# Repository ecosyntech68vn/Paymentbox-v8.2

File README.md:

# EcoSynTech PaymentBox V8.2 — Complete Package

**Production-ready hardware + firmware** cho hệ thống tự động hóa thu tiền VietQR
qua phone Android + ESP32 watchdog.

Tác giả: TA QUANG THUAN — CEO/CTO EcoSynTech Global
Ngày: 20/05/2026

---

## Cấu trúc package

```
EcoSynTech_PaymentBox_V8.2_complete/
├── README.md                          ← Bạn đang đọc
├── docs/                              ← Documentation
│   ├── FEASIBILITY.md                  Đánh giá khả thi E và F
│   ├── AUDIT_V8_1.md                   11 lỗi tìm thấy trong V8.1
│   ├── 01_SCHEMATIC_V8_1.md            Schematic V8.1 (deprecated)
│   ├── 01_LAYOUT_V8_1.md               Layout V8.1 (deprecated)
│   ├── SCHEMATIC_V8_2.md               ★ Schematic V8.2 production
│   └── GAS_ENDPOINTS_V8_2.md           ★ Spec backend GAS hỗ trợ firmware
│
├── hardware/                          ← PCB V8.2 fab-ready
│   ├── paymentbox_v8_2_jlcpcb.zip      ★ Upload thẳng JLCPCB
│   ├── pcb_layout_v8_2.png             Layout visual (6 zones)
│   ├── board.step                      3D model cho case design
│   ├── board_top.pdf                   Top view PDF
│   ├── BOM_E_watchdog.csv              BOM phương án E
│   ├── BOM_F_full.csv                  BOM phương án F
│   ├── Pick_Place_F.csv                CPL cho SMT
│   ├── gerber/                         Gerber files
│   ├── drill/                          Drill files
│   ├── components_v8_2.py              Component placement source
│   └── nets_v8_2.py                    Netlist source
│
└── firmware/                          ← ESP-IDF V5.x firmware
    ├── README.md                       Build instructions
    ├── TEST_REPORT.md                  ★ 68/68 tests pass, 0 cppcheck warnings
    ├── CMakeLists.txt
    ├── sdkconfig.defaults
    ├── partitions.csv
    ├── main/
    │   ├── main.c                      Entry point
    │   └── include/paymentbox_config.h  Centralized config
    ├── tests/                          ★ Host-side unit tests
    │   ├── test_config_server.c        33 tests pass
    │   └── test_ota_updater.c          35 tests pass
    └── components/
        ├── event_bus/                  Pub/sub FreeRTOS queue
        ├── wifi_manager/               STA + AP fallback
        ├── config_server/              ★ HTTP form 192.168.4.1
        ├── ota_updater/                ★ esp_https_ota từ GAS
        ├── phone_poller/               Poll phone /health 30s
        ├── gas_poller/                 Poll GAS heartbeat 60s
        ├── led_status/                 5-state machine 3-LED PWM
        ├── buzzer/                     Beep patterns
        ├── lcd_ui/                     I2C LCD 16x2
        ├── battery_monitor/            ADC + USB-lost detection
        └── sd_logger/                  NDJSON log + rotation
```

│
└── backend/                          ← GAS V9.5 backend endpoints (mới 5/2026)
    └── gas_v9_5/
        ├── README.md                  Hướng dẫn deploy vào GAS Editor
        ├── TEST_REPORT.md             ★ 42/42 unit tests pass
        ├── gas_v9_5_paymentbox_endpoints.js  ★ Code copy vào GAS
        └── test_gas_endpoints.js      Node.js local tests

★ = milestone V8.2 production-ready

---

## Quick start — 4 bước

### 1. Order PCB (1 ngày)
Upload `hardware/paymentbox_v8_2_jlcpcb.zip` lên JLCPCB:
- 5 boards, 2-layer, ENIG, HASL, 1.6mm
- Cost: ~$8 + ship $10 = **~450k VND total**

### 2. Order components (1 ngày, song song)
Dùng `hardware/BOM_E_watchdog.csv` đặt LCSC hoặc Shopee VN:
- Tổng linh kiện E: **~193k VND** mỗi board
- Plus pin 18650 protected 2500mAh: +50k VND
- Plus phone Android cũ: +400k VND
→ **Tổng ~700k VND/unit**

### 3. Lắp ráp + test hardware (1 buổi)
Theo `docs/SCHEMATIC_V8_2.md` section 7 (Safety checklist 10 điểm).
- Cấp USB-C → đo +5V_SAFE = 4.8-4.9V
- Cắm pin đúng → BAT+ = 3-4.2V
- **Cắm pin ngược → +5V_SAFE = 0V** (verify chống ngược cực)

### 4. Build + flash firmware (30 phút)
```bash
cd firmware
. $IDF_PATH/export.sh
idf.py set-target esp32
idf.py build
idf.py -p /dev/ttyUSB0 flash monitor
```

Reboot lần đầu → AP "PaymentBox-Setup" → mở `http://192.168.4.1` → nhập WiFi + phone IP → reboot vào STA mode → vận hành.

---

## Tính năng đã có

✅ **Hardware**:
- ESP32-WROOM-32 + đầy đủ peripheral
- USB-C input + PPTC fuse + SMBJ5.0CA TVS (chống sét)
- AO3401 P-FET (chống ngược cực pin)
- TP4056 sạc Li-ion + MT3608 boost 3.7→5V
- Pin 18650 external qua JST connector
- ADC battery monitor + USB-lost detection
- 3 LED indicator + buzzer + LCD 16x2
- I2C bus mở rộng, SPI cho SD card
- (Optional F) ATECC608B HMAC + microSD + relay reset phone

✅ **Firmware** (2654 LOC C):
- Event bus FreeRTOS pub/sub 8 subscribers
- WiFi STA + AP fallback config
- **HTTP config server** captive portal (Vietnamese UTF-8 form)
- **OTA update từ GAS** với anti-downgrade + boot sanity 60s + rollback
- Phone health poller 30s
- GAS heartbeat poller 60s
- 5-state LED state machine (IDLE/OK/WARN/ALERT/CRITICAL)
- Buzzer alert patterns
- LCD UI 2Hz refresh
- Battery monitor ADC + USB-lost dV/dt detection
- SD logger NDJSON với rotation

✅ **Testing**:
- 68/68 host-side unit tests pass
- 0 cppcheck warnings (warning, style, performance, portability)
- Hardware test plan trong `firmware/TEST_REPORT.md`

---

## Chưa làm (TODO)

| Feature | Mức | Khi nào cần |
|---|---|---|
| ATECC608B driver firmware | High | Phương án F production |
| HMAC sign transaction trước khi push GAS | High | Phương án F |
| Battery check trước OTA (skip nếu < 3.5V) | Med | Sau khi field test 1 tháng |
| SHA256 verify firmware từ GAS | Med | Bảo mật cao hơn |
| Mobile app config qua BLE | Low | Phương án F UX nâng cao |
| 2.4" TFT thay LCD 16x2 | Low | Phương án F UX nâng cao |
| SOP conformal coating spray | High (production) | Trước khi giao khách F |
| Hộp ABS IP65 + EPDM gasket | High (production) | Trước khi giao khách F |

---

## Liên hệ

Mọi câu hỏi / báo lỗi → TA QUANG THUAN
- Telegram: @AIThucChien_bot (cho hỗ trợ)
- Email/SĐT: liên hệ EcoSynTech Global

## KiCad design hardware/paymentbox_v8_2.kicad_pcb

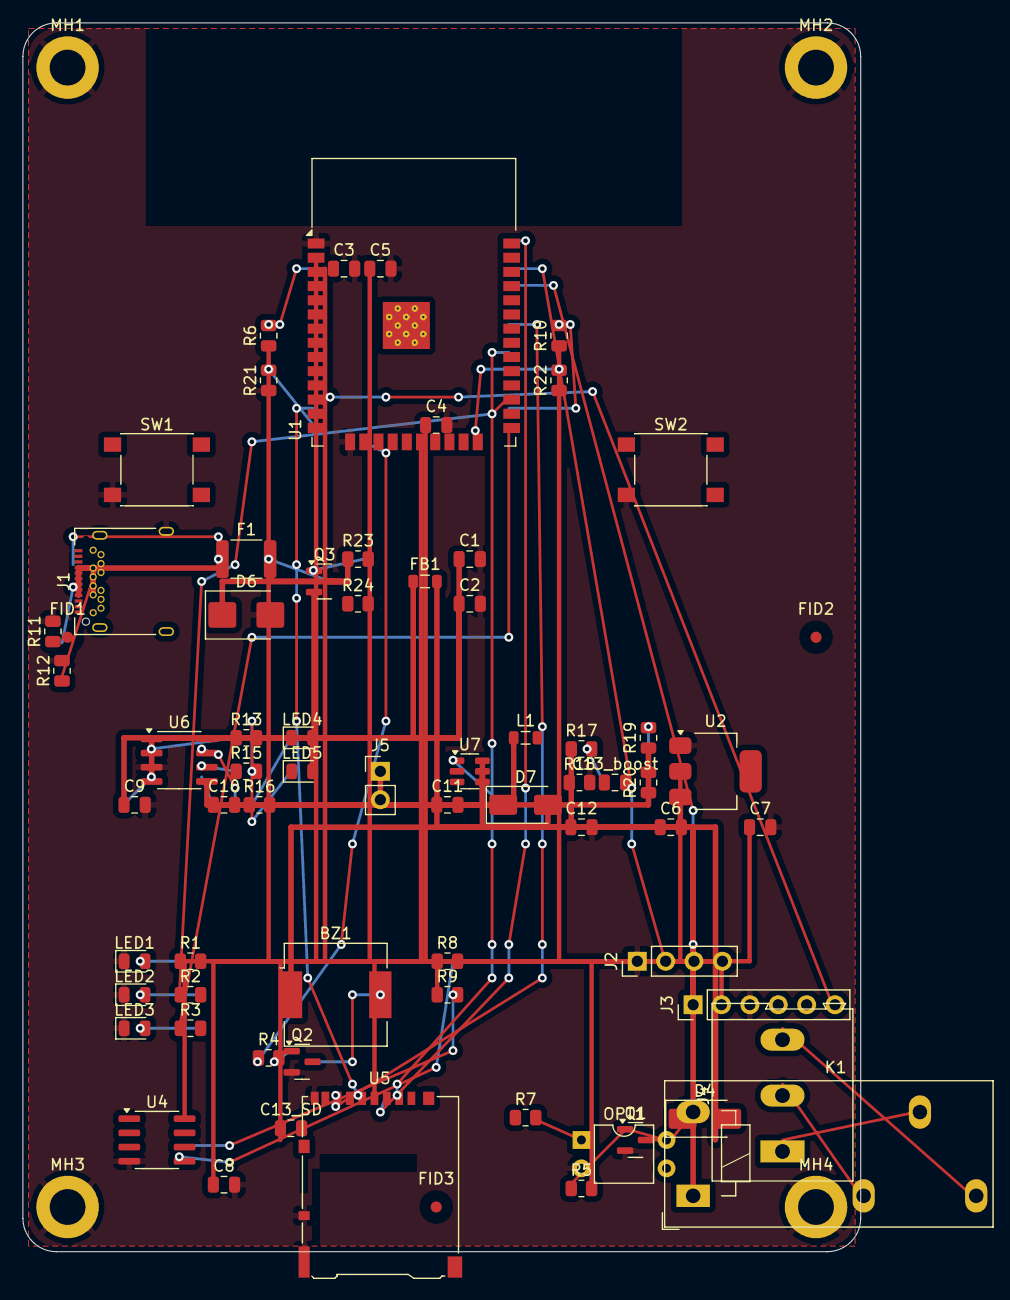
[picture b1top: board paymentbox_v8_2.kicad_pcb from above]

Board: 2 copper layers, 75.0 x 110.0 mm, 74 parts (0 on the bottom side), 45 nets.

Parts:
BZ1: BUZZER_5V; Buzzer_CUI_CPT-9019S-SMT
C1, C5, C9, C10, C13_SD: 10uF; C_0805_2012Metric
C2, C3, C4, C7, C8, C13_boost: 100nF; C_0805_2012Metric
C6, C11, C12: 22uF; C_0805_2012Metric
D4, D7: SS14; D_SMA
D6: SMBJ5.0CA; D_SMB
F1: PPTC_500mA; Fuse_1812_4532Metric
FB1: FB_1k; L_0805_2012Metric
FID1, FID2, FID3: FID; Fiducial_1mm_Mask3mm
J1: USB-C; USB_C_Receptacle_Amphenol_12401548E4-2A
J2: UART; PinHeader_1x04_P2.54mm_Vertical
J3: EXP; PinHeader_1x06_P2.54mm_Vertical
J4: RELAY_OUT; TerminalBlock_Altech_AK300-3_P5.00mm
J5: BAT; PinHeader_1x02_P2.54mm_Vertical
K1: SRD-05VDC; Relay_SPDT_Schrack-RT1-FormC_RM5mm
L1: 4.7uH; L_0805_2012Metric
LED1: RED; LED_0805_2012Metric
LED2: GREEN; LED_0805_2012Metric
LED3: BLUE; LED_0805_2012Metric
LED4: CHRG_RED; LED_0805_2012Metric
LED5: DONE_GRN; LED_0805_2012Metric
MH1, MH2, MH3, MH4: M3; MountingHole_3.2mm_M3_DIN965_Pad
OPT1: PC817; DIP-4_W7.62mm
Q1, Q2: MMBT3904; SOT-23
Q3: AO3401; SOT-23
R1, R2, R3: 220R; R_0805_2012Metric
R4, R5, R7, R15, R16: 1k; R_0805_2012Metric
R6, R10, R21, R22, R24: 10k; R_0805_2012Metric
R8, R9: 4.7k; R_0805_2012Metric
R11, R12: 5.1k; R_0805_2012Metric
R13: 1.2k; R_0805_2012Metric
R17: 22k; R_0805_2012Metric
R18: 3k; R_0805_2012Metric
R19, R23: 100k; R_0805_2012Metric
R20: 47k; R_0805_2012Metric
SW1: RESET; SW_Push_1P1T_NO_6x6mm_H9.5mm
SW2: BOOT; SW_Push_1P1T_NO_6x6mm_H9.5mm
U1: ESP32-WROOM-32
U2: AMS1117-3.3; SOT-223-3_TabPin2
U4: ATECC608B; SOIC-8_3.9x4.9mm_P1.27mm
U5: microSD; microSD_HC_Hirose_DM3AT-SF-PEJM5
U6: TP4056; SOIC-8_3.9x4.9mm_P1.27mm
U7: MT3608; SOT-23-6

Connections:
+3V3: C3.1, C4.1, C5.1, C7.1, C8.1, C13_SD.1, J2.4, J3.2, R5.2, R6.1, R8.1, R9.1, R10.1, U1.2, U1.20, U2.2, U4.8, U5.4
+5V_PROT_RAW: D6.1, F1.2, Q3.3, R23.1
+5V_SAFE: C1.1, C2.1, C9.1, FB1.1, LED4.2, LED5.2, Q3.2, U6.4
+5V_SYS: BZ1.1, C6.1, C12.1, D4.2, D7.2, FB1.2, J3.1, K1.A1, R17.1, U2.3, U7.5
+5V_USB_RAW: F1.1, J1.A4, J1.A9, J1.B4, J1.B9
ADC_BAT: R19.2, R20.1, U1.4
BAT+: C10.1, C11.1, J5.1, L1.1, R19.1, U6.5, U7.6
BOOST_FB: C13_boost.1, R17.2, R18.1, U7.3
BOOST_SW: D7.1, L1.2, U7.1
BUZZ_BASE: Q2.1, R4.2
BUZZ_COLLECTOR: BZ1.2, Q2.3
BUZZ_DRV: R4.1, U1.16
CHRG_LED: LED4.1, R16.2
CHRG_N: R16.1, U6.7
DONE_LED: LED5.1, R15.2
DONE_N: R15.1, U6.6
EN_RST: R6.2, SW1.1, U1.3
EXP_GPIO: J3.6, U1.12
GND: C1.2, C2.2, C3.2, C4.2, C5.2, C6.2, C7.2, C8.2, C9.2, C10.2, C11.2, C12.2, C13_SD.2, C13_boost.2, D6.2, J1.A1, J1.A12, J1.B1, J1.B12, J1.S1, J2.1, J3.3, J5.2, LED1.1, LED2.1, LED3.1, MH1.1, MH2.1, MH3.1, MH4.1, OPT1.2, Q1.2, Q2.2, R11.2, R12.2, R13.2, R18.2, R20.2, R21.1, R22.1, R24.2, SW1.2, SW2.2, U1.1, U1.15, U1.39, U2.1, U4.4, U5.6, U5.9, U5.10, U5.11, U6.3, U7.2
GPIO0_BOOT: R10.2, SW2.1, U1.26
I2C_SCL: J3.5, R9.2, U1.37, U4.6
I2C_SDA: J3.4, R8.2, U1.34, U4.5
LED_B_ANODE: LED3.2, R3.2
LED_B_DRV: R3.1, U1.25
LED_G_ANODE: LED2.2, R2.2
LED_G_DRV: R2.1, U1.27
LED_R_ANODE: LED1.2, R1.2
LED_R_DRV: R1.1, R21.2, U1.14
PROG: R13.1, U6.2
Q3_GATE: Q3.1, R23.2, R24.1
RELAY_COIL_LOW: D4.1, K1.A2, Q1.3
RELAY_COM: J4.1, K1.11
RELAY_DRV: R7.1, R22.2, U1.24
RELAY_NC: J4.2, K1.12
RELAY_NO: J4.3, K1.14
RELAY_OPTO_LED: OPT1.1, R7.2
RELAY_OPTO_OUT: OPT1.4, Q1.1, R5.1
SPI_CS_SD: U1.30, U5.2
SPI_MISO: U1.32, U5.7
SPI_MOSI: U1.38, U5.3
SPI_SCK: U1.13, U5.5
UART_RX: J2.3, U1.35
UART_TX: J2.2, U1.36
USB_CC1: J1.A5, R11.1
USB_CC2: J1.B5, R12.1

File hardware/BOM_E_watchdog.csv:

Comment,Designator,Footprint,LCSC Part #,Quantity
1.2k,R13,R_0805_2012Metric,C17520,1
100k,"R19,R23",R_0805_2012Metric,C17407,2
100nF,"C13_boost,C2,C3,C4,C7",C_0805_2012Metric,C49678,5
10k,"R10,R21,R22,R24,R6",R_0805_2012Metric,C17414,5
10uF,"C1,C10,C5,C9",C_0805_2012Metric,C15850,4
1k,"R15,R16,R4",R_0805_2012Metric,C17513,3
220R,"R1,R2,R3",R_0805_2012Metric,C17557,3
22k,R17,R_0805_2012Metric,C17557,1
22uF,"C11,C12,C6",C_0805_2012Metric,C45783,3
3k,R18,R_0805_2012Metric,C17561,1
4.7k,"R8,R9",R_0805_2012Metric,C17475,2
4.7uH,L1,L_0805_2012Metric,C407457,1
47k,R20,R_0805_2012Metric,C17475,1
5.1k,"R11,R12",R_0805_2012Metric,C23186,2
AMS1117-3.3,U2,SOT-223-3_TabPin2,C6186,1
AO3401,Q3,SOT-23,C15127,1
BAT,J5,PinHeader_1x02_P2.54mm_Vertical,C124375,1
BLUE,LED3,LED_0805_2012Metric,C72041,1
BOOT,SW2,SW_Push_1P1T_NO_6x6mm_H9.5mm,C318884,1
BUZZER_5V,BZ1,Buzzer_CUI_CPT-9019S-SMT,C95298,1
CHRG_RED,LED4,LED_0805_2012Metric,C84256,1
DONE_GRN,LED5,LED_0805_2012Metric,C72043,1
ESP32-WROOM-32,U1,ESP32-WROOM-32,C701343,1
EXP,J3,PinHeader_1x06_P2.54mm_Vertical,C124380,1
FB_1k,FB1,L_0805_2012Metric,C1017,1
GREEN,LED2,LED_0805_2012Metric,C72043,1
MMBT3904,Q2,SOT-23,C20526,1
MT3608,U7,SOT-23-6,C47773,1
PPTC_500mA,F1,Fuse_1812_4532Metric,C369317,1
RED,LED1,LED_0805_2012Metric,C84256,1
RESET,SW1,SW_Push_1P1T_NO_6x6mm_H9.5mm,C318884,1
SMBJ5.0CA,D6,D_SMB,C8975,1
SS14,D7,D_SMA,C2480,1
TP4056,U6,SOIC-8_3.9x4.9mm_P1.27mm,C16581,1
UART,J2,PinHeader_1x04_P2.54mm_Vertical,C124378,1
USB-C,J1,USB_C_Receptacle_Amphenol_12401548E4-2A,C168688,1

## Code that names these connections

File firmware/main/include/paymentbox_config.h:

/**
 * paymentbox_config.h — EcoSynTech PaymentBox V8.2 firmware config
 *
 * Tập trung MỌI hằng số tại đây. Không hardcode trong source.
 */
#pragma once

#include "driver/gpio.h"
#include "hal/adc_types.h"

// ============================================================
// VERSION
// ============================================================
#define FW_VERSION             "1.0.0"
#define FW_BUILD_DATE          __DATE__ " " __TIME__
#define HW_VERSION             "V8.2"

// ============================================================
// GPIO MAPPING — KHÔNG TỰ ĐỔI (phải đồng bộ với SCHEMATIC_V8_2.md)
// ============================================================

// LED status
#define PIN_LED_R              GPIO_NUM_12  // Đỏ — Sự cố
#define PIN_LED_G              GPIO_NUM_4   // Xanh lá — OK
#define PIN_LED_B              GPIO_NUM_2   // Xanh dương — Hoạt động

// Buzzer
#define PIN_BUZZER             GPIO_NUM_13

// Relay (phương án F only)
#define PIN_RELAY              GPIO_NUM_15

// I2C bus (LCD + ATECC608B)
#define PIN_I2C_SDA            GPIO_NUM_21
#define PIN_I2C_SCL            GPIO_NUM_22
#define I2C_PORT_NUM           I2C_NUM_0
#define I2C_FREQ_HZ            100000   // 100kHz
#define I2C_ADDR_LCD           0x27     // PCF8574 LCD backpack
#define I2C_ADDR_ATECC         0x60     // ATECC608B (F only)

// SPI bus (microSD)
#define PIN_SPI_SCK            GPIO_NUM_14
#define PIN_SPI_MOSI           GPIO_NUM_23
#define PIN_SPI_MISO           GPIO_NUM_19
#define PIN_SPI_CS_SD          GPIO_NUM_5

// ADC battery sense
#define PIN_ADC_BAT            ADC_CHANNEL_0   // GPIO36 / SENSOR_VP
#define BAT_DIVIDER_RATIO      3.13f           // V_BAT = ADC * 3.13

// UART debug
#define UART_NUM               UART_NUM_0
#define UART_BAUDRATE          115200

// ============================================================
// NETWORK
// ============================================================

// WiFi (qua wifi_manager — đọc từ NVS khi flash, hoặc qua AP config)
#define WIFI_DEFAULT_SSID      "EcoSynTech-Setup"
#define WIFI_DEFAULT_PSK       ""              // empty = open AP
#define WIFI_AP_FALLBACK_NAME  "PaymentBox-Setup"
#define WIFI_AP_PASSWORD       "ecosyntech"    // WPA2 PSK cho AP mode; đọc từ NVS key "wifi.ap_psk" nếu có
#define WIFI_CONNECT_TIMEOUT_MS 30000
#define WIFI_RECONNECT_DELAY_MS 5000

// Phone (BankNotify-App on Android)
// Tự discover qua mDNS hoặc set qua AP config UI
#define PHONE_DEFAULT_IP       "192.168.1.50"  // override via NVS
#define PHONE_HEALTH_URL       "http://%s:8765/api/v1/health"
#define PHONE_RECENT_URL       "http://%s:8765/api/v1/transactions/recent"
#define PHONE_POLL_INTERVAL_MS 60000           // 60s (1 phút quét 1 lần)
#define PHONE_TIMEOUT_MS       5000

// GAS backend (V9.5)
// Cần config khi flash production
#define GAS_BASE_URL           "https://script.google.com/macros/s/SHEET_ID/exec"
#define GAS_HEARTBEAT_PATH     "?action=getHeartbeat&device_id=%s"
#define GAS_POLL_INTERVAL_MS   60000           // 60s
#define GAS_TIMEOUT_MS         10000

// Telegram alert (optional — cần set token + chat_id trước khi dùng)
#define TELEGRAM_BOT_TOKEN      ""                // Bot token từ @BotFather — set trong NVS key "tg.token" nếu có
#define TELEGRAM_CHAT_ID        ""                // Chat ID để nhận alert — set trong NVS key "tg.chat_id"

// OTA update
#define OTA_CHECK_INTERVAL_MS  (24 * 3600 * 1000)   // 24h
#define OTA_CHECK_TIMEOUT_MS   15000
#define OTA_DOWNLOAD_TIMEOUT_MS 120000              // 2 phút
#define OTA_BOOT_SANITY_MS     60000                // Đợi 60s sau boot → mark valid

// Device identification
#define DEVICE_ID_PREFIX       "ESG-PB-"
#define DEVICE_ID_LEN          16              // ESG-PB-XXXXXXXX (8 hex từ MAC)

// ============================================================
// STATE MACHINE THRESHOLDS
// ============================================================

// Tính từ lần phone respond cuối:
#define HEALTH_OK_WINDOW_MS    60000           // <60s từ lần ping cuối = OK
#define HEALTH_WARN_WINDOW_MS  180000          // 1-3 phút = WARN (vàng)
#define HEALTH_ALERT_WINDOW_MS 300000          // 3-5 phút = ALERT (đỏ)
// > 5 phút = CRITICAL

// Battery thresholds
#define BAT_FULL_V             4.10f
#define BAT_LOW_V              3.40f
#define BAT_CRITICAL_V         3.00f

// ============================================================
// FREERTOS TASK CONFIG
// ============================================================
#define TASK_STACK_SMALL       2048
#define TASK_STACK_MEDIUM      4096
#define TASK_STACK_LARGE       8192

#define PRIO_LOW               2
#define PRIO_MED               5
#define PRIO_HIGH              10
#define PRIO_CRITICAL          15

// ============================================================
// SD CARD LOGGING
// ============================================================
#define SD_LOG_PATH            "/sdcard/paymentbox.log"
#define SD_LOG_MAX_BYTES       1048576         // 1MB → rotate
#define SD_LOG_ROTATE_KEEP     5               // keep 5 old logs

// ============================================================
// PROTOTYPING TOGGLES
// ============================================================
#define ENABLE_PHONE_POLLER    1
#define ENABLE_GAS_POLLER      1
#define ENABLE_LCD_UI          1
#define ENABLE_SD_LOG          0   // disable nếu phương án E không lắp SD
#define ENABLE_RELAY_CTRL      0   // F only — luôn 0 cho phương án E
#define ENABLE_BATTERY_MONITOR 1
#define ENABLE_CONFIG_SERVER   1   // HTTP server cho AP mode setup
#define ENABLE_OTA             1   // OTA firmware update qua GAS
#define ENABLE_TELEGRAM_ALERT  0   // Bật Telegram alert khi GAS down / bat critical

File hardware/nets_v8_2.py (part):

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        # Let me make it: +5V_SAFE in net carries LED5.2, then LED5.1 connects via R15 to TP4056 STDBY pin
    ],

    # TP4056 PROG (charge current set) — pin 2 to GND via R13
    "PROG_R": [
        ("U6", "2"),    # TP4056 PROG (pin 2)
        ("R13", "1"),
    ],
    # R13 high side wired in this net, low side to GND. Wait need separate:
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        ("SW1", "1"),   # Reset button
    ],

    "GPIO0_BOOT": [
        ("U1", "26"),
        ("R10", "2"),
        ("SW2", "1"),
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    # ============================================================
    # Expansion
    # ============================================================
    "EXP_GPIO": [("U1", "12"), ("J3", "6")],

    # ============================================================
    # +5V_SAFE special: PC817 emitter + R5 high side
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
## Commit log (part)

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2026-05-20 Audit V8.2: fix 24 bugs, add Quick Wins, Medium optimizations, backend rollout, architecture improvements
    Bug fixes (24): NVS error handling, HTTPS crt_bundle, duplicate init, DFM annular ring,
    battery check before OTA, ADC curve_fitting migration, C13_boost fix, trace width,
    partition warning, GAS backend pattern match, decoupling/edge clearance, MT3608 formula,
    event_bus timestamp, USB lost debounce, GAS early-break, buzzer 30min timeout,
    deep sleep on critical, C13 naming, phone_poller headers, sd_logger rename,
    WiFi wait logging, phone_ip validation, .gitignore
2026-05-21 Add event bus filtering, state machine refactor, unit tests, Telegram alert
    Event bus: new event_bus_subscribe_filtered() lets subscribers receive only
    relevant event types (main, buzzer, led_status, ota_updater). Reduces queue
    pressure and prevents drops.
    LED state machine: extract subsys_t struct, separate compute_state(&sys),
    add on_state_enter() for clean entry/exit actions.
    Unit tests: 10 state transition tests (led_status) + 12 battery threshold/USB
